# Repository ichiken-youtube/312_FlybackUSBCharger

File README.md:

# FlybackUSBCharger
本リポジトリはイチケンが以下の動画で製作した自作フライバックコンバータ回路のリポジトリです。

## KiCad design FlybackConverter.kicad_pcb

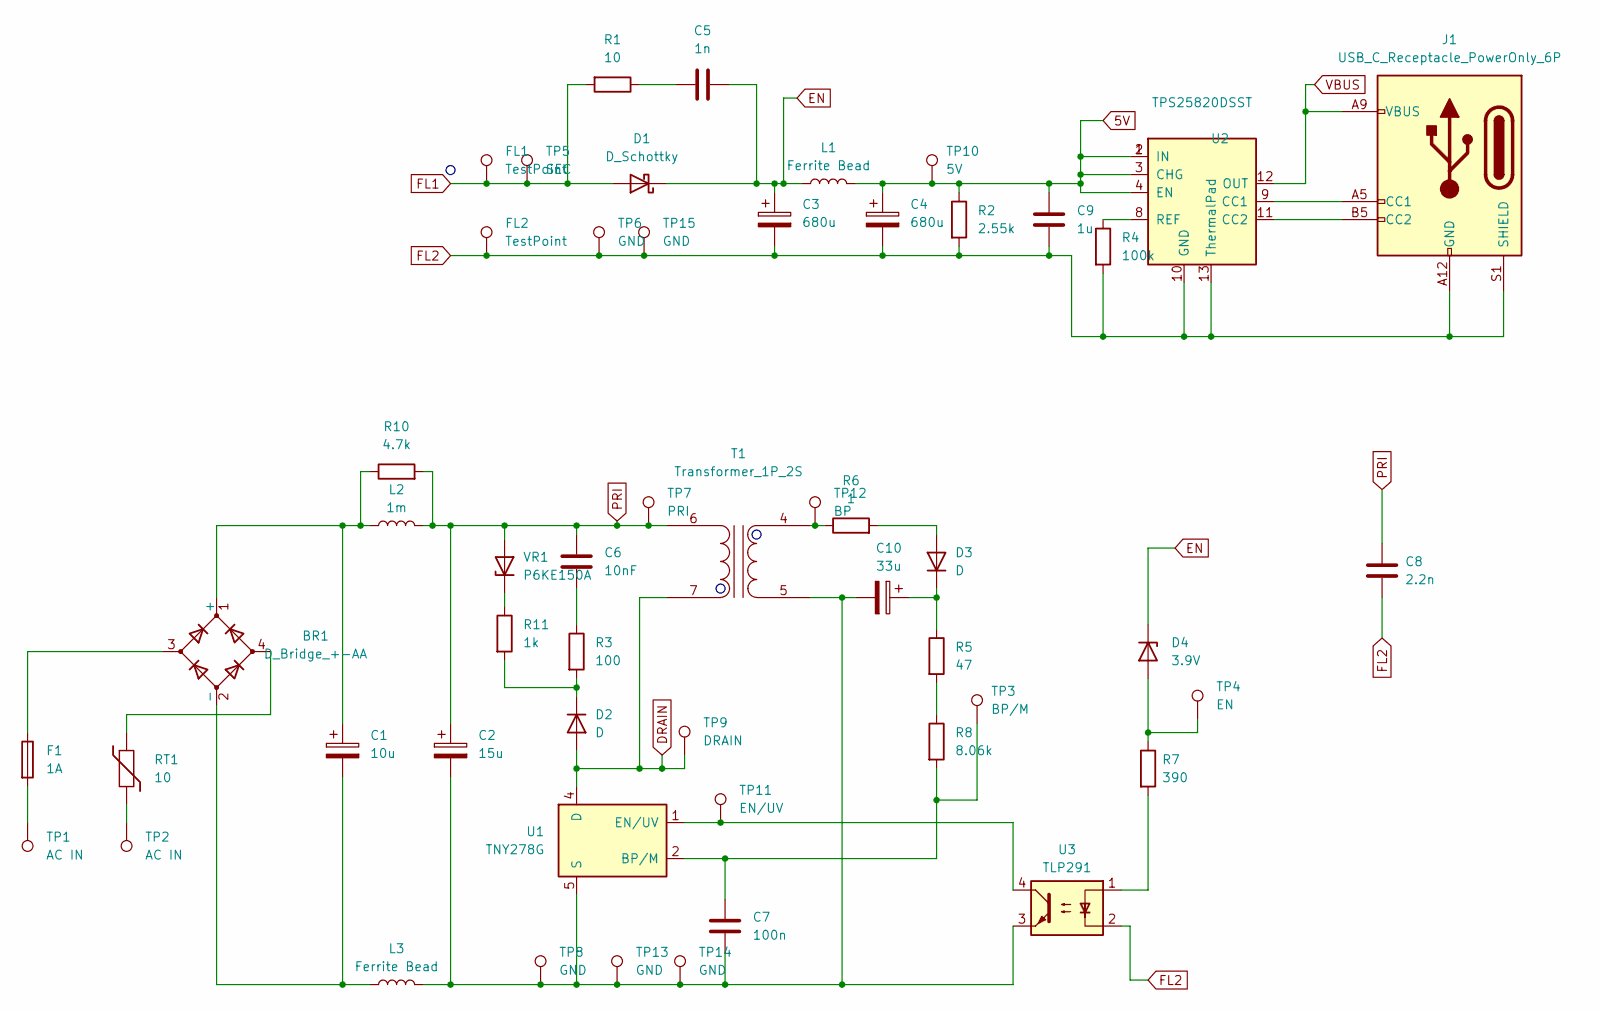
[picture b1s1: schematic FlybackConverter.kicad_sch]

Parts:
BR1: D_Bridge_+-AA; TO-269AA
C1: 10u; CP_Radial_D10.0mm_P5.00mm
C2: 15u; CP_Radial_D12.5mm_P5.00mm
C3, C4: 680u; CP_Radial_D8.0mm_P3.50mm
C5: 1n; C_0805_2012Metric
C6: 10nF; C_0805_2012Metric
C7: 100n; C_1206_3216Metric
C8: 2.2n; C_Disc_D10.5mm_W5.0mm_P10.00mm
C9: 1u; C_0805_2012Metric
C10: 33u; CP_Radial_D5.0mm_P2.50mm
D1: D_Schottky; D_PowerDI-5
D2: D; D_SMA
D3: D; D_SMF
D4: 3.9V; D_SOD-323
F1: 1A; C_Rect_L7.2mm_W4.5mm_P5.00mm_FKS2_FKP2_MKS2_MKP2
FL1, FL2: TestPoint; TestPoint_Loop_D1.80mm_Drill1.0mm_Beaded
J1: USB_C_Receptacle_PowerOnly_6P; USB-C-SMD_TYPE-C-6P
L1, L3: Ferrite Bead; R_Axial_DIN0309_L9.0mm_D3.2mm_P12.70mm_Horizontal
L2: 1m; L_Radial_D9.5mm_P5.00mm_Fastron_07HVP
R1: 10; R_0805_2012Metric
R2: 2.55k; R_0805_2012Metric
R3: 100; R_1206_3216Metric
R4: 100k; R_0603_1608Metric
R5: 47; R_0603_1608Metric
R6: 1; R_0603_1608Metric
R7: 390; R_0603_1608Metric
R8: 8.06k; R_0603_1608Metric
R10: 4.7k; R_0603_1608Metric
R11: 1k; R_1206_3216Metric
RT1: 10; C_Disc_D10.5mm_W5.0mm_P7.50mm
T1: Transformer_1P_2S; B66206W1110T001
TP1, TP2: AC IN; TestPoint_Loop_D1.80mm_Drill1.0mm_Beaded
TP3: BP/M; TestPoint_Loop_D1.80mm_Drill1.0mm_Beaded
TP4: EN; TestPoint_Loop_D1.80mm_Drill1.0mm_Beaded
TP5: SEC; TestPoint_Loop_D1.80mm_Drill1.0mm_Beaded
TP6, TP8, TP13, TP14, TP15: GND; TestPoint_Loop_D1.80mm_Drill1.0mm_Beaded
TP7: PRI; TestPoint_Loop_D1.80mm_Drill1.0mm_Beaded
TP9: DRAIN; TestPoint_Loop_D1.80mm_Drill1.0mm_Beaded
TP10: 5V; TestPoint_Loop_D1.80mm_Drill1.0mm_Beaded
TP11: EN/UV; TestPoint_Loop_D1.80mm_Drill1.0mm_Beaded
TP12: BP; TestPoint_Loop_D1.80mm_Drill1.0mm_Beaded
U1: TNY278G; PowerIntegrations_SMD-8C
U2: TPS25820DSST; TPS25820
U3: TLP291; SOIC-4_4.55x2.6mm_P1.27mm
VR1: P6KE150A; D_DO-15_P10.16mm_Horizontal

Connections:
5V: C4.1, C9.1, L1.2, R2.1, TP10.1, U2.1 (IN), U2.2 (IN), U2.3 (CHG), U2.4 (EN)
DRAIN: D2.2 (A), T1.7 (AB), TP9.1, U1.4 (D)
EN: C3.1, C5.2, D1.1 (K), D4.1 (K), L1.1
FL1: D1.2 (A), FL1.1, R1.2, TP5.1
FL2: C3.2, C4.2, C8.2, C9.2, FL2.1, J1.A12 (GND), J1.B12 (GND), J1.S1 (SHIELD), R2.2, R4.2, TP6.1, TP15.1, U2.10 (GND), U2.13 (ThermalPad), U3.2
unnamed: BR1.1 (+), C1.1, L2.1, R10.1
unnamed: BR1.2 (-), C1.2, L3.1
unnamed: BR1.3, F1.1
unnamed: BR1.4, RT1.1
unnamed: C5.1, R1.1
unnamed: C6.2, R3.1
unnamed: D2.1 (K), R3.2, R11.2
unnamed: D3.2 (A), R6.2
unnamed: C10.1, D3.1 (K), R5.1
unnamed: D4.2 (A), R7.1, TP4.1
unnamed: F1.2, TP1.1
unnamed: J1.A5 (CC1), U2.9 (CC1)
unnamed: J1.B5 (CC2), U2.11 (CC2)
unnamed: R5.2, R8.1
unnamed: R7.2, U3.1
unnamed: RT1.2, TP2.1
unnamed: C2.2, C7.2, C10.2, L3.2, T1.5 (SA), TP8.1, TP13.1, TP14.1, U1.5 (S), U1.6 (S), U1.7 (S), U1.8 (S), U3.3
unnamed: R6.1, T1.4 (SB), TP12.1
unnamed: C7.1, R8.2, TP3.1, U1.2 (BP/M)
unnamed: TP11.1, U1.1 (EN/UV), U3.4
unnamed: R4.1, U2.8 (REF)
unnamed: R11.1, VR1.1 (K)
PRI: C2.1, C6.1, C8.1, L2.2, R10.2, T1.6 (AA), TP7.1, VR1.2 (A)
VBUS: J1.A9 (VBUS), J1.B9 (VBUS), U2.12 (OUT)

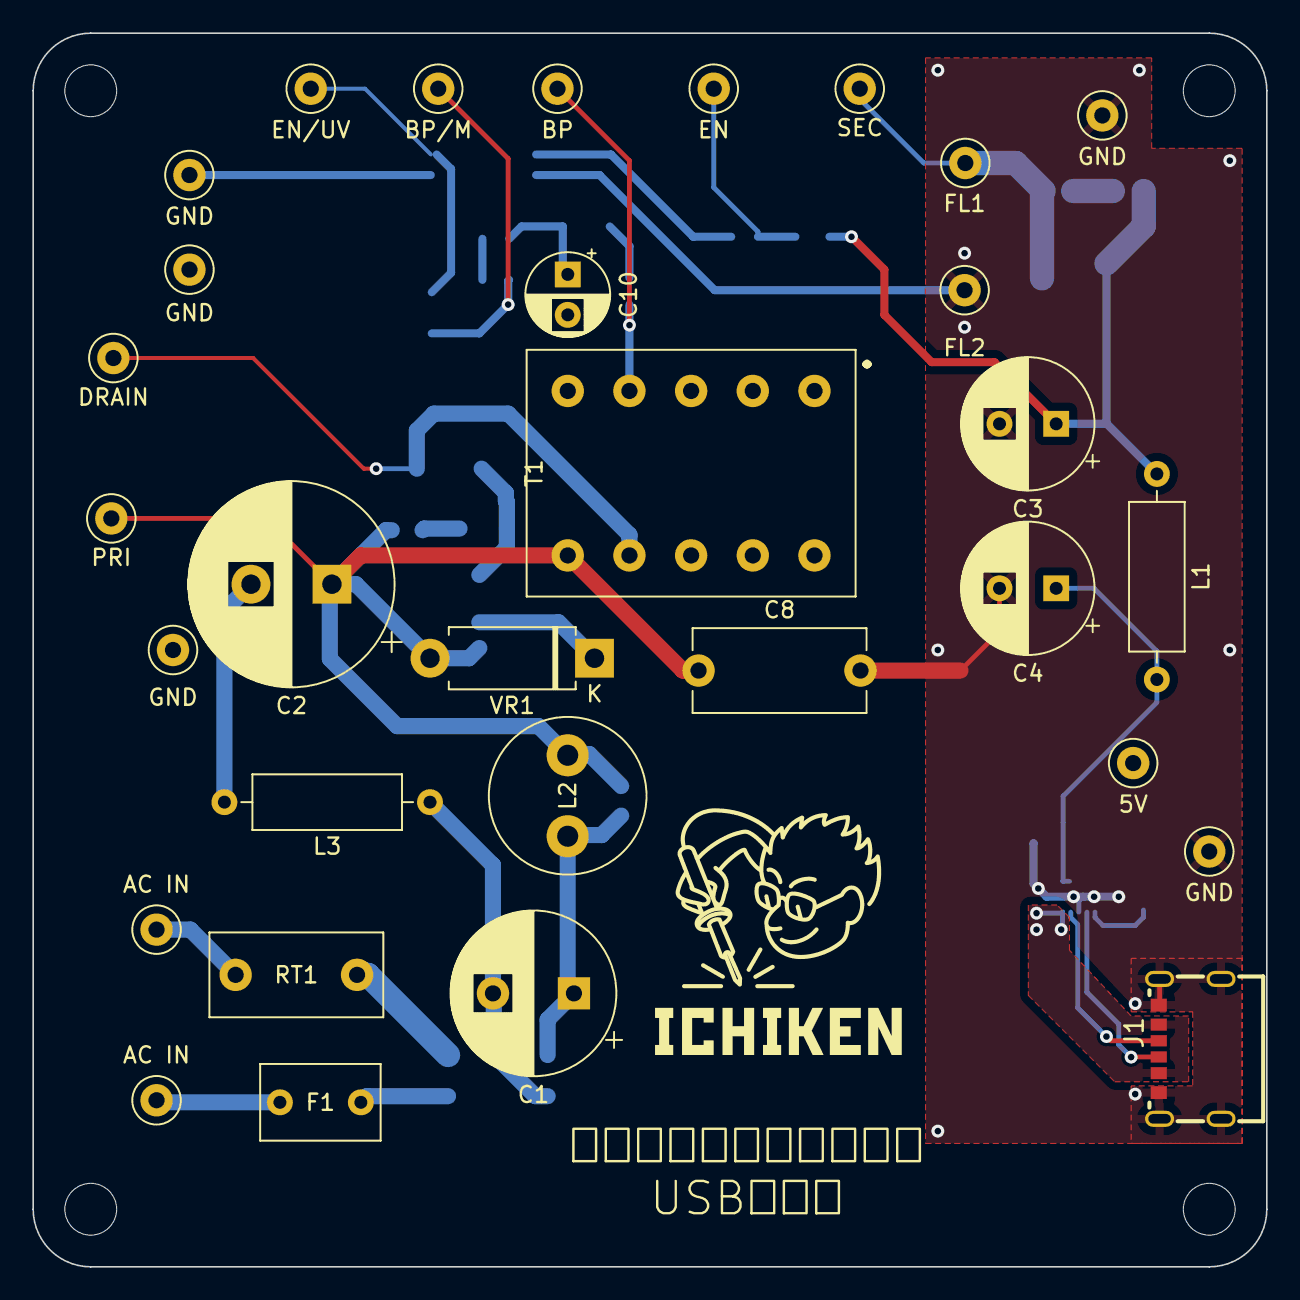
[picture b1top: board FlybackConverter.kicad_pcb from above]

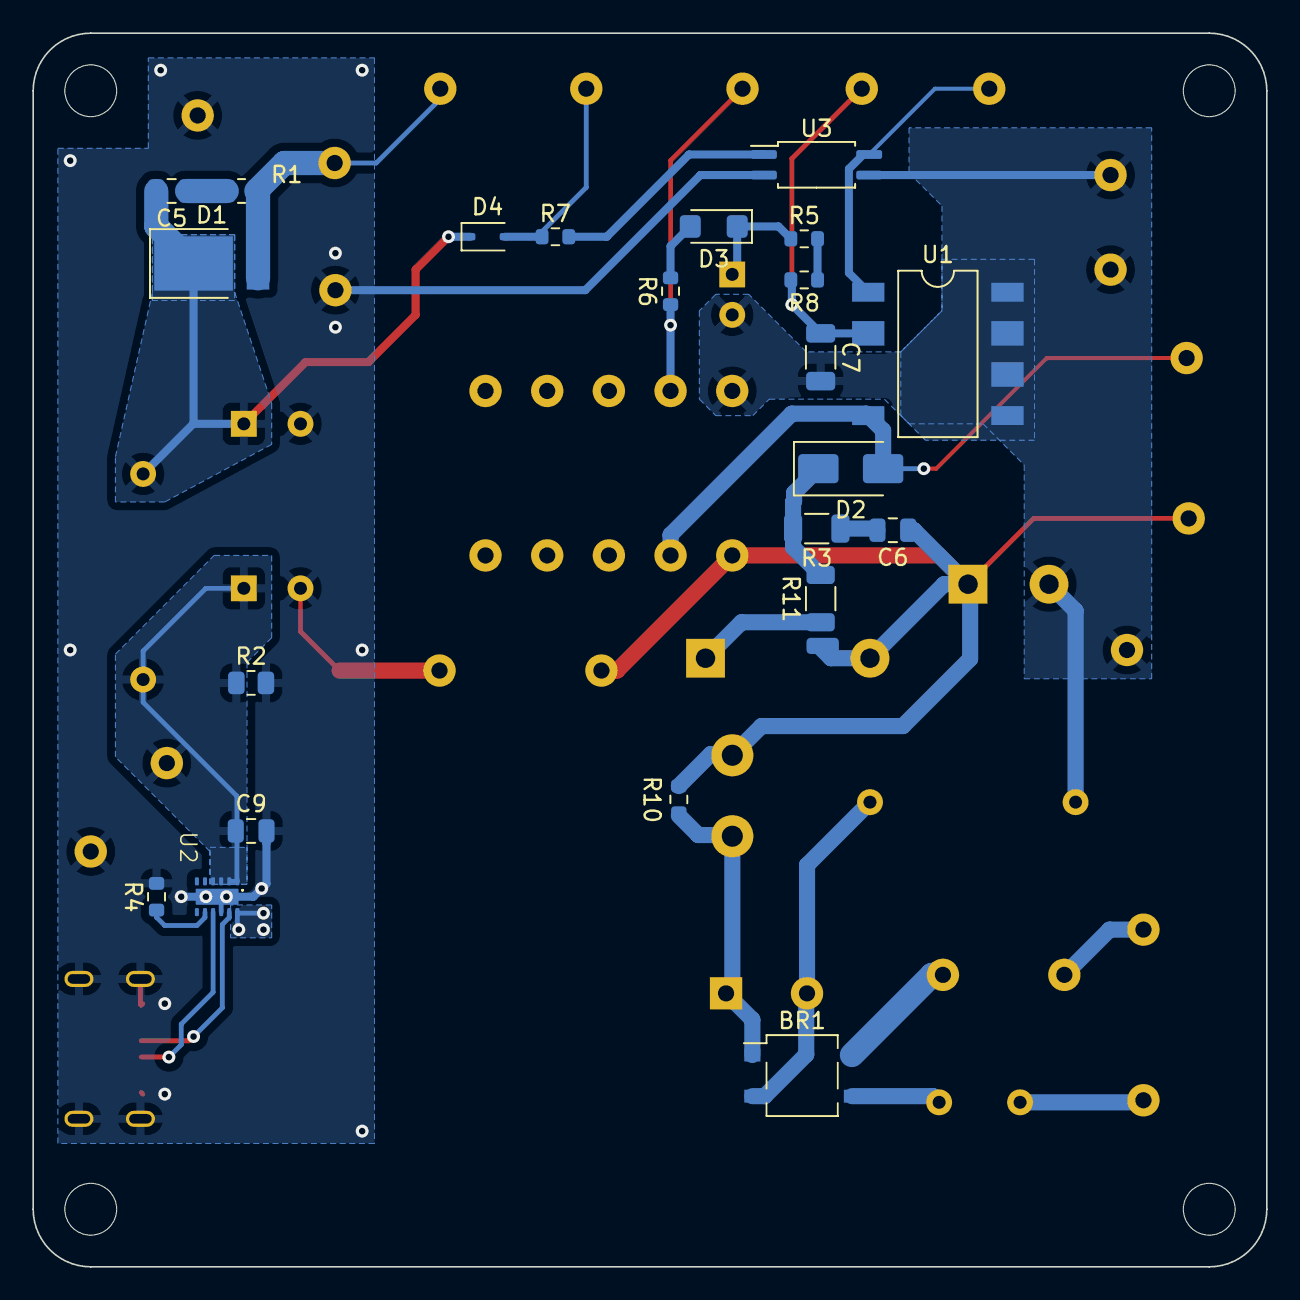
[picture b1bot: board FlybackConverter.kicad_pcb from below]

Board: 2 copper layers, 76.2 x 76.2 mm, 53 parts (22 on the bottom side), 29 nets.

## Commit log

2024-10-09 スイッチングICをLNK6428Kに変更
2024-10-09 フットプリント追加
2024-10-10 フットプリント設定
2024-10-10 トランスのフットプリント修正、FL1,2に合わせてシンボル変更
2024-10-10 add readme
2024-10-10 TypeC仮配置 #1
2024-10-11 USBコントローラ配置 #1
2024-10-11 AC側配線幅1mmで統一 fix #4
2024-10-11 パスコン設置 fix #1
2024-10-11 可変抵抗接続用に配線を引き出せる穴を追加 fix #2
2024-10-11 トランスのフットプリントを10pinに修正
2024-10-11 TP追加 fix #3
2024-10-11 U1のサーマルパッドのリリーフなし
2024-10-15 C7のフットプリントを1206に変更 #5
2024-10-16 B66206W1110T001フットプリント作成 #6
2024-10-16 トランスのフットプリント修正、それに合わせて部品配置も調整 fix #6
2024-10-18 Net-(T1-AA)の塗りつぶし無し、配線に置き換え #8
2024-10-18 配線位置微修正、DRC問題無し #8
2024-10-18 出力をTypeCに変更したのに合わせてreadme修正
2024-10-18 スナバ配置変更 fix #8
2024-10-31 トランス周辺のネット名変更
2024-11-15 コイル極性メモ
2024-11-15 2024/11/15
2024-11-18 回路修正
2024-11-18 TP以外大体配置できた #10
2024-11-19 TP配置
2024-11-19 VR1バイパス用パッドのネット変更
2024-12-02 回路図を現物に合わせて修正 #12
2024-12-02 readme途中
2024-12-02 readme途中 #12
2024-12-02 アウトラインのみ作った
2024-12-03 トランス組み立て手順
2024-12-03 動作確認手順を記述
2024-12-03 動作確認手順など fix #12
2024-12-03 改行位置など修正 #12
2024-12-03 細かいパラメータ修正
2024-12-04 画像にUEWの径を追記
2024-12-06 R7(FBツェナー部分)抵抗値修正 #12
2025-08-18 readme 組み立て手順削除
2025-08-18 埋め込み動画コメントアウト
2025-08-18 readme用画像削除
2025-08-19 動画埋め込み
